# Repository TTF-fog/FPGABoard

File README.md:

# S3GA
an FPGA board based on the ICE40UP5K and the ESP32S3-Mini (module). 

Allows for wireless functionality (maybe even programming?) using the ESP32S3-M and IO using the iCE

## Why?
- i wasn't able to find any boards that integrated wireless functionality with the ICE40UP5K, so i decided to make one!

# Setup
- I recommend getting the QFN packages assembled, but you can smd solder them if you want
- for code flashing, read # Usage below
# Usage
- the S3 can be developed for using Arduino / ESP-IDF and programmed with the respective tools
    - the iCE can be developed with [iCEStorm](https://github.com/YosysHQ/icestorm) or [iCEcube2](https://www.latticesemi.com/en/Products/DesignSoftwareAndIP/FPGAandLDS/iCEcube2) and programmed using the bitstream generated by the [Diamond Programmer](https://www.latticesemi.com/en/Products/DesignSoftwareAndIP/ProgrammingAndConfigurationSw/Programmer).
     To flash use [SPIFFS](https://docs.espressif.com/projects/esp-idf/en/stable/esp32/api-reference/storage/spiffs.html) to save a file under the name "stream" for the generated bitstream, and then use the [flash code](Firmware/mcu-flash)

# Sublinks
- [BOM](BOM.csv)
- [Gerbers](Hardware/production_files/production_files/GERBER-FPGABoard.zip)
- [Zine](Zine.pdf)
- [Schematic PDF](Hardware/design_files/Schematic.pdf)
# Pinout

# Images

note: if the images don't load, you can see them at [images](Images)

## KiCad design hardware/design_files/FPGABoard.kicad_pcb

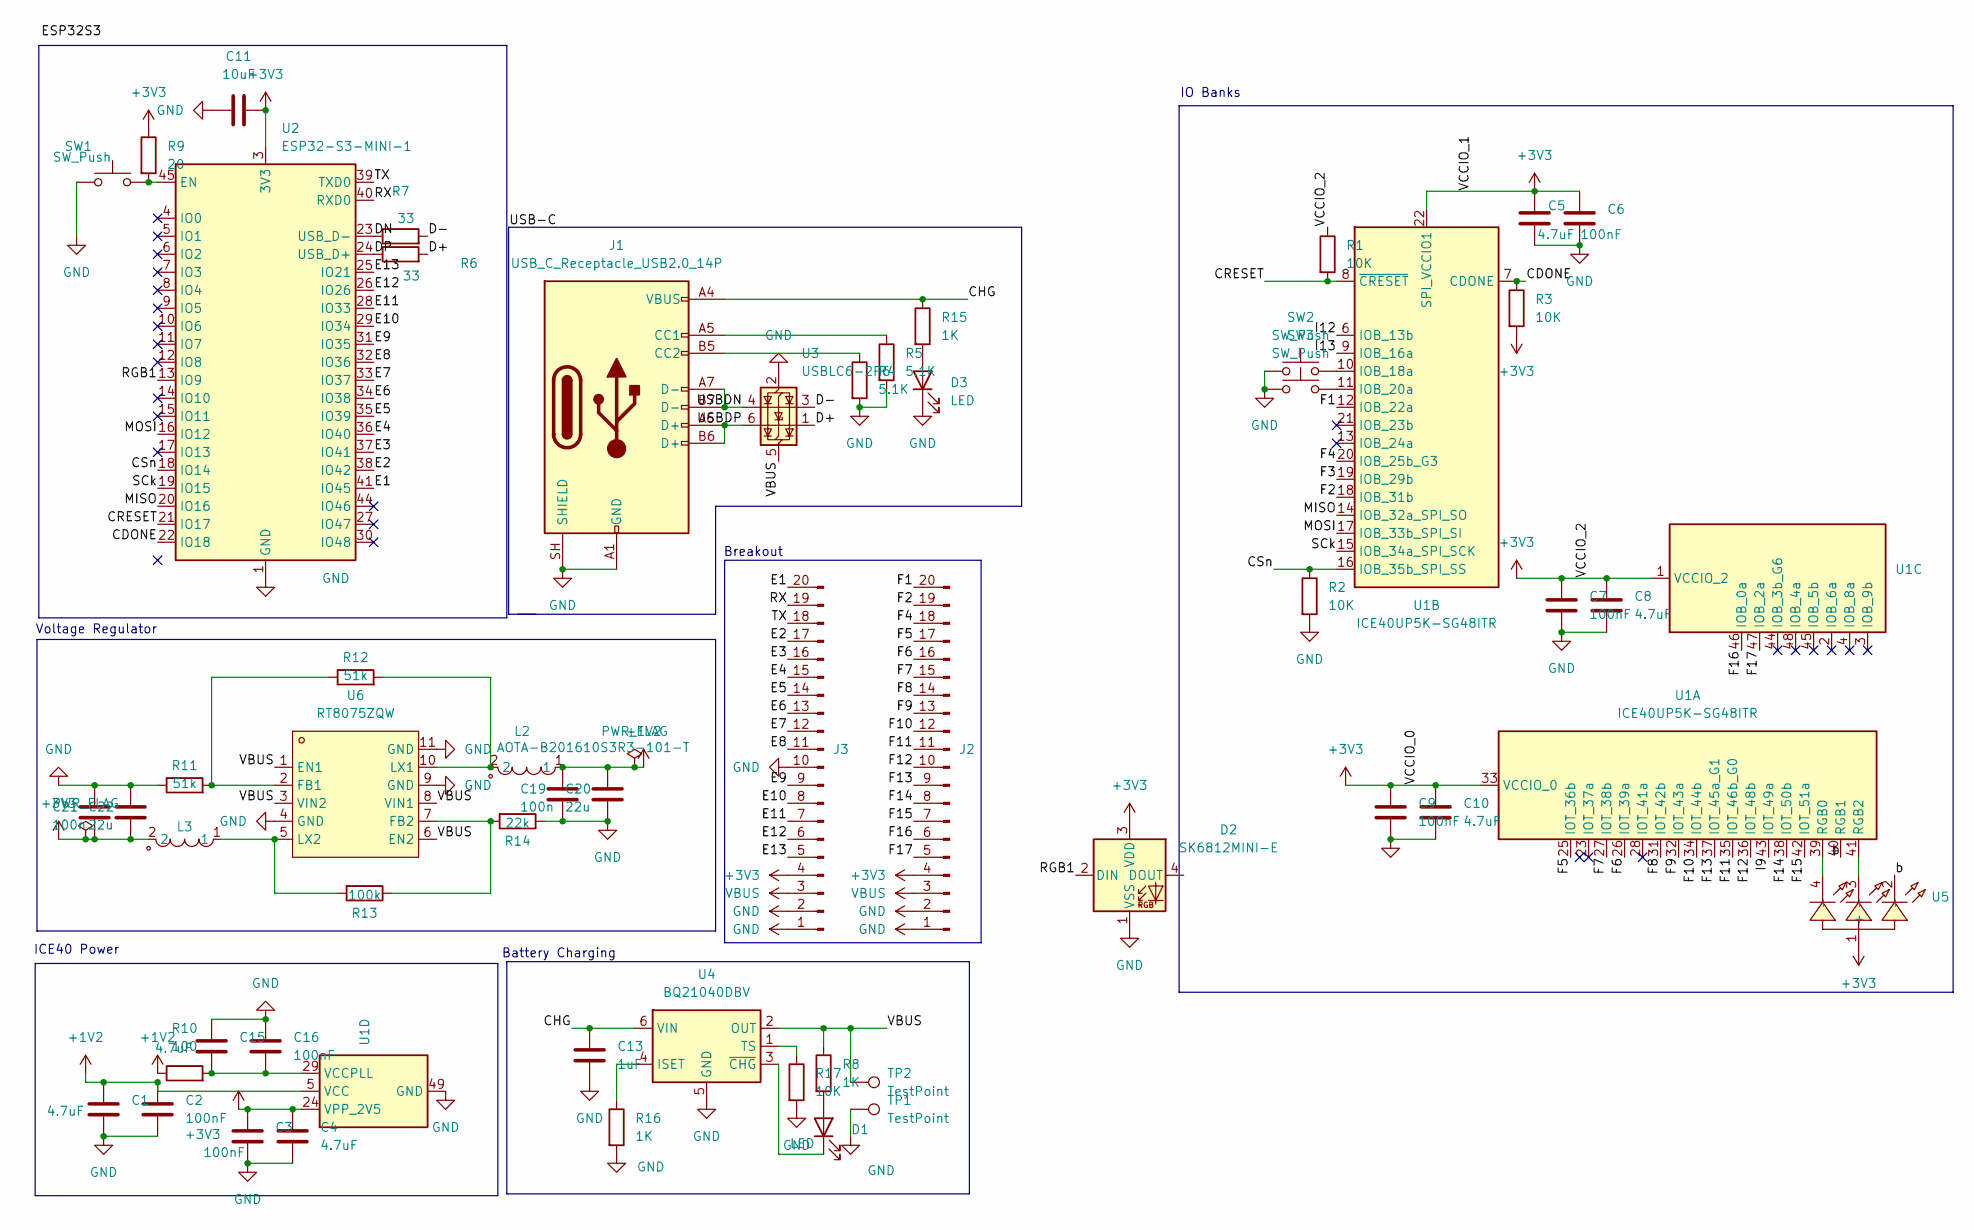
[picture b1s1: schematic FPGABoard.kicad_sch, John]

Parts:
C1, C4, C5, C8, C10, C15: 4.7uF; C_0402_1005Metric
C2, C3, C6, C7, C9, C16: 100nF; C_0402_1005Metric
C11: 10uF; C_0402_1005Metric
C13: 1uF; C_0402_1005Metric
C19, C21: 100n; C_0402_1005Metric
C20, C22: 22u; C_0402_1005Metric
D1, D3: LED; LED_0402_1005Metric
D2: SK6812MINI-E; LED_SK6812MINI-E_3.2x2.8mm_P1.5mm_ReverseMount
J1: USB_C_Receptacle_USB2.0_14P; USB_C_Receptacle_HRO_TYPE-C-31-M-12
J2, J3: Conn_01x20_Pin; PinHeader_1x20_P2.54mm_Vertical
L2, L3: AOTA-B201610S3R3-101-T; L_0603_1608Metric_Pad1.05x0.95mm_HandSolder; LCSC Part C42411119
R1, R2, R3, R17: 10K; R_0402_1005Metric
R4, R5: 5.1K; R_0402_1005Metric
R6, R7: 33; R_0402_1005Metric
R8, R15, R16: 1K; R_0402_1005Metric
R9: 20; R_0402_1005Metric
R10: 100; R_0402_1005Metric
R11, R12: 51k; R_0402_1005Metric
R13: 100k; R_0402_1005Metric
R14: 22k; R_0402_1005Metric
SW1, SW2, SW3: SW_Push; SW_Push_1P1T_NO_CK_KMR2
TP1, TP2: TestPoint; TestPoint_Pad_D1.0mm
U1: ICE40UP5K-SG48ITR; QFN-48-1EP_7x7mm_P0.5mm_EP5.6x5.6mm
U2: ESP32-S3-MINI-1; ESP32-S2-MINI-1
U3: USBLC6-2P6; SOT-666
U4: BQ21040DBV; SOT-23-6
U5: TJ-S1608SW6TDSLCCYRGB-A5; LED-ARRAY-SMD_4P-L1.6-W0.8-BL-FD; MPN TJ-S1608SW6TDSLCCYRGB-A5; LCSC Part C5356078
U6: RT8075ZQW; WDFN-10_L3.0-W3.0-P0.50-BL-EP; LCSC Part C250416

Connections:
+1V2: C1.1, C2.1, C19.1, C20.1, L2.1, R10.1, U1.5 (VCC), U1.30 (VCC)
+3V3: C3.1, C4.1, C5.1, C6.1, C7.1, C8.1, C9.1, C10.1, C11.2, C21.2, C22.2, D2.3 (VDD), J2.4, J3.4, L3.2, R1.1, R3.2, R9.1, U1.1 (VCCIO_2), U1.22 (SPI_VCCIO1), U1.24 (VPP_2V5), U1.33 (VCCIO_0), U2.3 (3V3), U5.1 (+)
/CDONE: R3.1, U1.7 (CDONE), U2.22 (IO18)
/CHG: C13.1, J1.A4 (VBUS), J1.A9 (VBUS), J1.B4 (VBUS), J1.B9 (VBUS), R15.1, U4.6 (VIN)
/CRESET: R1.2, U1.8 (~CRESET), U2.21 (IO17)
/CSn: R2.1, U1.16 (IOB_35b_SPI_SS), U2.18 (IO14)
/D+: R6.2, U3.1 (I/O1)
/D-: R7.2, U3.3 (I/O2)
/DN: R7.1, U2.23 (USB_D-)
/DP: R6.1, U2.24 (USB_D+)
/E1: J3.20, U2.41 (IO45)
/E2: J3.17, U2.38 (IO42)
/E3: J3.16, U2.37 (IO41)
/E4: J3.15, U2.36 (IO40)
/E5: J3.14, U2.35 (IO39)
/E6: J3.13, U2.34 (IO38)
/E7: J3.12, U2.33 (IO37)
/E8: J3.11, U2.32 (IO36)
/E9: J3.9, U2.31 (IO35)
/E10: J3.8, U2.29 (IO34)
/E11: J3.7, U2.28 (IO33)
/E12: J3.6, U2.26 (IO26)
/E13: J3.5, U2.25 (IO21)
/F1: J2.20, U1.12 (IOB_22a)
/F2: J2.19, U1.18 (IOB_31b)
/F3: U1.19 (IOB_29b)
/F4: J2.18, U1.20 (IOB_25b_G3)
/F5: J2.17, U1.25 (IOT_36b)
/F6: J2.16, U1.26 (IOT_39a)
/F7: J2.15, U1.27 (IOT_38b)
/F8: J2.14, U1.31 (IOT_42b)
/F9: J2.13, U1.32 (IOT_43a)
/F10: J2.12, U1.34 (IOT_44b)
/F11: J2.11, U1.35 (IOT_46b_G0)
/F12: J2.10, U1.36 (IOT_48b)
/F13: J2.9, U1.37 (IOT_45a_G1)
/F14: J2.8, U1.38 (IOT_50b)
/F15: J2.7, U1.42 (IOT_51a)
/F16: J2.6, U1.46 (IOB_0a)
/F17: J2.5, U1.47 (IOB_2a)
/I9: U1.43 (IOT_49a)
/I12: U1.6 (IOB_13b)
/I13: U1.9 (IOB_16a)
/I17: U1.21 (IOB_23b)
/I18: U1.13 (IOB_24a)
/MISO: U1.14 (IOB_32a_SPI_SO), U2.20 (IO16)
/MOSI: U1.17 (IOB_33b_SPI_SI), U2.16 (IO12)
/RGB1: D2.2 (DIN), U2.13 (IO9)
/RX: J3.19, U2.40 (RXD0)
/SCk: U1.15 (IOB_34a_SPI_SCK), U2.19 (IO15)
/TX: J3.18, U2.39 (TXD0)
/USBDN: J1.A7 (D-), J1.B7 (D-), U3.4 (I/O2)
/USBDP: J1.A6 (D+), J1.B6 (D+), U3.6 (I/O1)
/b: U1.40 (RGB1), U5.2 (-)
GND: C1.2, C2.2, C3.2, C4.2, C5.2, C6.2, C7.2, C8.2, C9.2, C10.2, C11.1, C13.2, C15.1, C16.1, C19.2, C20.2, C21.1, C22.1, D2.1 (VSS), D3.1 (K), J1.A1 (GND), J1.A12 (GND), J1.B1 (GND), J1.B12 (GND), J1.SH (SHIELD), J2.1, J2.2, J3.1, J3.2, J3.10, R2.2, R4.2, R5.2, R11.1, R14.1, R16.2, R17.2, SW1.1, SW2.1, SW3.1, TP1.1 (1_1), U1.49 (GND), U2.1 (GND), U2.2 (GND), U2.42 (GND), U2.43 (GND), U2.46 (GND), U2.47 (GND), U2.48 (GND), U2.49 (GND), U2.50 (GND), U2.51 (GND), U2.52 (GND), U2.53 (GND), U2.54 (GND), U2.55 (GND), U2.56 (GND), U2.57 (GND), U2.58 (GND), U2.59 (GND), U2.60 (GND), U2.61 (GND), U2.62 (GND), U2.63 (GND), U2.64 (GND), U2.65 (GND), U3.2 (GND), U4.5 (GND), U6.4 (GND), U6.9 (GND), U6.11 (GND)
unnamed: D1.2 (A), R8.2
unnamed: D1.1 (K), U4.3 (~CHG)
unnamed: D3.2 (A), R15.2
unnamed: J1.A5 (CC1), R5.1
unnamed: J1.B5 (CC2), R4.1
unnamed: U1.39 (RGB0), U5.4 (-)
unnamed: U1.41 (RGB2), U5.3 (-)
unnamed: SW2.2, U1.10 (IOB_18a)
unnamed: SW3.2, U1.11 (IOB_20a)
unnamed: C15.2, C16.2, R10.2, U1.29 (VCCPLL)
unnamed: R9.2, SW1.2, U2.45 (EN)
unnamed: R16.1, U4.4 (ISET)
unnamed: R17.1, U4.1 (TS)
unnamed: R11.2, R12.1, U6.2 (FB1)
unnamed: R13.1, R14.2, U6.7 (FB2)
unnamed: L2.2, R12.2, U6.10 (LX1)
unnamed: L3.1, R13.2, U6.5 (LX2)
VBUS: J2.3, J3.3, R8.1, TP2.1 (1_1), U3.5 (VBUS), U4.2 (OUT), U6.1 (EN1), U6.3 (VIN2), U6.6 (EN2), U6.8 (VIN1)

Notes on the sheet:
IO Banks
Battery Charging
Breakout
ICE40 Power
Voltage Regulator

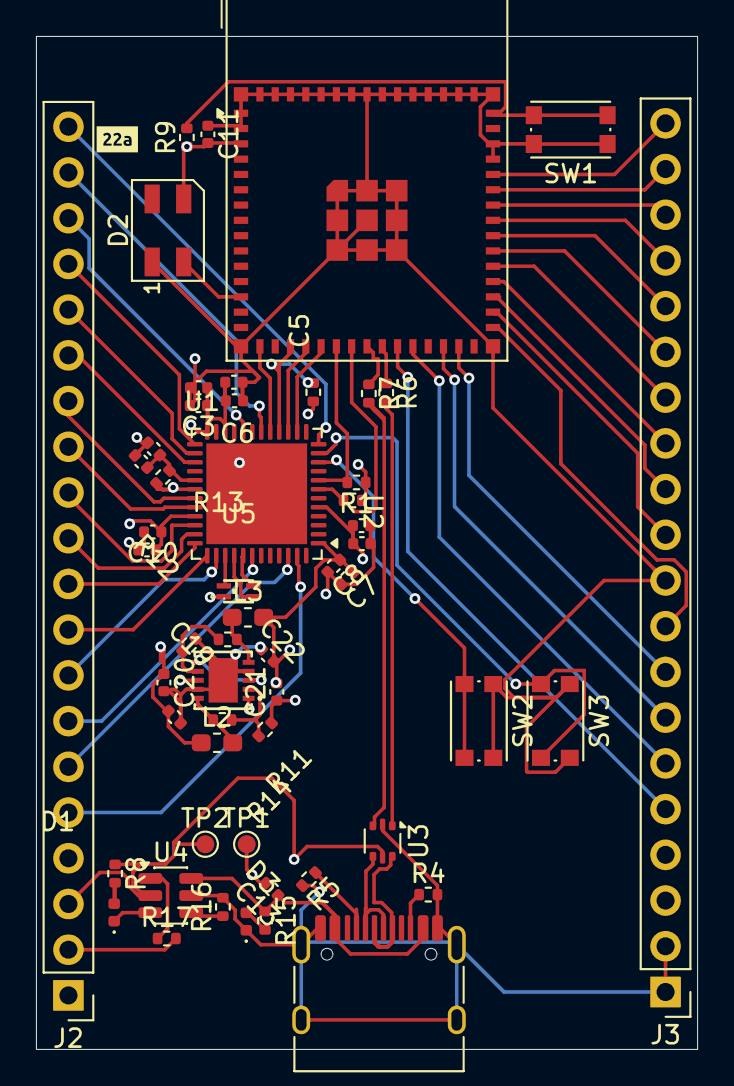
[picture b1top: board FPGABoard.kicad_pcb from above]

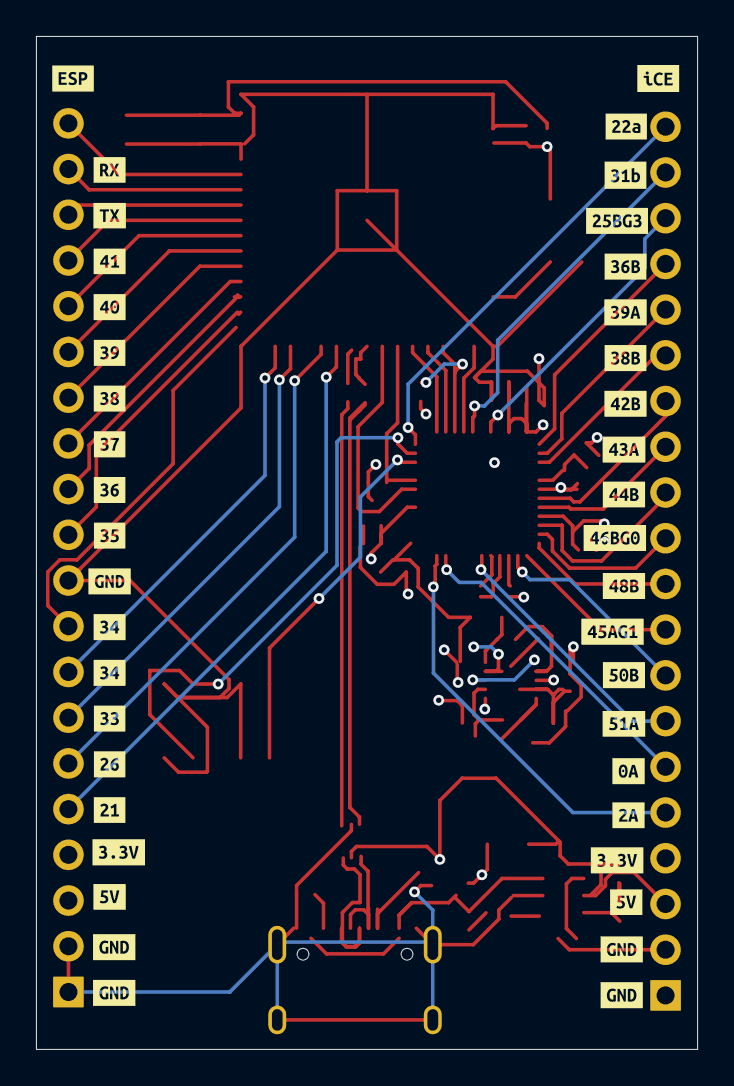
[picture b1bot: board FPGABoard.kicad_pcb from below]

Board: 4 copper layers, 36.7 x 56.3 mm, 96 parts (41 on the bottom side), 67 nets.

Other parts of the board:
kibuzzard-6A1AFA27, kibuzzard-6A1AFA27#2: G***; kibuzzard-6A1AFA27
kibuzzard-6A1AFA79, kibuzzard-6A1AFA79#2: G***; kibuzzard-6A1AFA79
kibuzzard-6A1AFA94, kibuzzard-6A1AFA94#2, kibuzzard-6A1AFA94#3, kibuzzard-6A1AFA94#4: G***; kibuzzard-6A1AFA94
kibuzzard-6A1AFB9A: G***; kibuzzard-6A1AFB9A
kibuzzard-6A1AFBC0: G***; kibuzzard-6A1AFBC0
kibuzzard-6A1AFC0F: G***; kibuzzard-6A1AFC0F
kibuzzard-6A1AFC22, kibuzzard-6A1AFC22#2: G***; kibuzzard-6A1AFC22
kibuzzard-6A1AFC53: G***; kibuzzard-6A1AFC53
kibuzzard-6A1AFC58: G***; kibuzzard-6A1AFC58
kibuzzard-6A1AFD1A: G***; kibuzzard-6A1AFD1A
kibuzzard-6A1AFD12: G***; kibuzzard-6A1AFD12
kibuzzard-6A1AFD34: G***; kibuzzard-6A1AFD34
kibuzzard-6A1AFD40: G***; kibuzzard-6A1AFD40
kibuzzard-6A1AFD49: G***; kibuzzard-6A1AFD49
kibuzzard-6A1AFD53: G***; kibuzzard-6A1AFD53
kibuzzard-6A1AFD64: G***; kibuzzard-6A1AFD64
kibuzzard-6A1AFD94: G***; kibuzzard-6A1AFD94
kibuzzard-6A1AFEE8: G***; kibuzzard-6A1AFEE8
kibuzzard-6A1AFEEE: G***; kibuzzard-6A1AFEEE
kibuzzard-6A1AFF00: G***; kibuzzard-6A1AFF00
kibuzzard-6A1AFF0B: G***; kibuzzard-6A1AFF0B
kibuzzard-6A1AFF2B: G***; kibuzzard-6A1AFF2B
kibuzzard-6A1AFF6D: G***; kibuzzard-6A1AFF6D
kibuzzard-6A1AFF8C: G***; kibuzzard-6A1AFF8C
kibuzzard-6A1AFF40: G***; kibuzzard-6A1AFF40
kibuzzard-6A1AFF78: G***; kibuzzard-6A1AFF78
kibuzzard-6A1AFFA5: G***; kibuzzard-6A1AFFA5
kibuzzard-6A1AFFB7: G***; kibuzzard-6A1AFFB7
kibuzzard-6A1B014D: G***; kibuzzard-6A1B014D
kibuzzard-6A1B016E: G***; kibuzzard-6A1B016E
kibuzzard-6A1B018E: G***; kibuzzard-6A1B018E
kibuzzard-6A1B0130: G***; kibuzzard-6A1B0130
kibuzzard-6A1B0165: G***; kibuzzard-6A1B0165
kibuzzard-6A1B0180: G***; kibuzzard-6A1B0180
kibuzzard-6A1B0204: G***; kibuzzard-6A1B0204
kibuzzard-6A1B0228: G***; kibuzzard-6A1B0228

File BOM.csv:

Comment,Designator,Footprint,LCSC,Quantity,Link
100,R10,R_0402_1005Metric,C25076,1,https://www.lcsc.com/product-detail/C25076.html
100k,R13,R_0402_1005Metric,C25741,1,https://www.lcsc.com/product-detail/C25741.html
100n,"C19,C21",C_0402_1005Metric,C1525,2,https://www.lcsc.com/product-detail/C1525.html
100nF,"C16,C2,C3,C6,C7,C9",C_0402_1005Metric,C1525,6,https://www.lcsc.com/product-detail/C1525.html
10K,"R1,R17,R2,R3",R_0402_1005Metric,C25744,4,https://www.lcsc.com/product-detail/C25744.html
10uF,C11,C_0402_1005Metric,C15525,1,https://www.lcsc.com/product-detail/C15525.html
1K,"R15,R16,R8",R_0402_1005Metric,C11702,3,https://www.lcsc.com/product-detail/C11702.html
1uF,C13,C_0402_1005Metric,C52923,1,https://www.lcsc.com/product-detail/C52923.html
20,R9,R_0402_1005Metric,C2004,1,https://www.lcsc.com/product-detail/C2004.html
22k,R14,R_0402_1005Metric,C25768,1,https://www.lcsc.com/product-detail/C25768.html
22u,"C20,C22",C_0402_1005Metric,C385994,2,https://www.lcsc.com/product-detail/C385994.html
33,"R6,R7",R_0402_1005Metric,C25105,2,https://www.lcsc.com/product-detail/C25105.html
4.7uF,"C1,C10,C15,C4,C5,C8",C_0402_1005Metric,C23733,6,https://www.lcsc.com/product-detail/C23733.html
5.1K,"R4,R5",R_0402_1005Metric,C25905,2,https://www.lcsc.com/product-detail/C25905.html
51k,"R11,R12",R_0402_1005Metric,C25794,2,https://www.lcsc.com/product-detail/C25794.html
AOTA-B201610S3R3-101-T,"L2,L3",L_0603_1608Metric_Pad1.05x0.95mm_HandSolder,C42411119,2,https://www.lcsc.com/product-detail/C42411119.html
BQ21040DBV,U4,SOT-23-6,C78978,1,https://www.lcsc.com/product-detail/C78978.html
ESP32-S3-MINI-1,U2,ESP32-S2-MINI-1,C2913206,1,https://www.lcsc.com/product-detail/C2913206.html
ICE40UP5K-SG48ITR,U1,QFN-48-1EP_7x7mm_P0.5mm_EP5.6x5.6mm,C2678152,1,https://www.lcsc.com/product-detail/C2678152.html
LED,"D1,D3",LED_0402_1005Metric,C71911,2,https://www.lcsc.com/product-detail/C71911.html
RT8075ZQW,U6,WDFN-10_L3.0-W3.0-P0.50-BL-EP,C250416,1,https://www.lcsc.com/product-detail/C250416.html
SW_Push,"SW1,SW2,SW3",SW_Push_1P1T_NO_CK_KMR2,C72443,3,https://www.lcsc.com/product-detail/C72443.html
TJ-S1608SW6TDSLCCYRGB-A5,U5,LED-ARRAY-SMD_4P-L1.6-W0.8-BL-FD,C5356078,1,https://www.lcsc.com/product-detail/C5356078.html
USBLC6-2P6,U3,SOT-666,C53059594,1,https://www.lcsc.com/product-detail/C53059594.html
USB_C_Receptacle_USB2.0_14P,J1,USB_C_Receptacle_HRO_TYPE-C-31-M-12,C165948,1,https://www.lcsc.com/product-detail/C165948.html
Conn_01x20_Pin,J3,PinHeader_1x20_P2.54mm_Vertical,,1,DNP
Conn_01x20_Pin,J2,PinHeader_1x20_P2.54mm_Vertical,,1,DNP
TestPoint,TP1,TestPoint_Pad_D1.0mm,,1,DNP
TestPoint,TP2,TestPoint_Pad_D1.0mm,,1,DNP
SK6812MINI-E,D2,LED_SK6812MINI_PLCC4_3.5x3.5mm_P1.75mm,,1,DNP

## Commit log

2026-05-30 updat
2026-05-31 the zine
2026-05-31 rearrange and reformat
2026-06-01 add links to bom
2026-06-06 update bom
2026-06-09 images got cooked for some reason
